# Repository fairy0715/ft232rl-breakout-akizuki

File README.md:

# ft232rl-breakout-akizuki

秋月電子製のFT232RLモジュール(通販コード:[101977](https://akizukidenshi.com/catalog/g/g101977/),[106693](https://akizukidenshi.com/catalog/g/g106693/))の互換基板です。

## 特徴
・接続端子をUSB mini-BからCに変更

・基本的に秋月電子で購入できる部品で作成可能

・表面実装部品を裏面に配置(本家と異なり、両面実装になっています)

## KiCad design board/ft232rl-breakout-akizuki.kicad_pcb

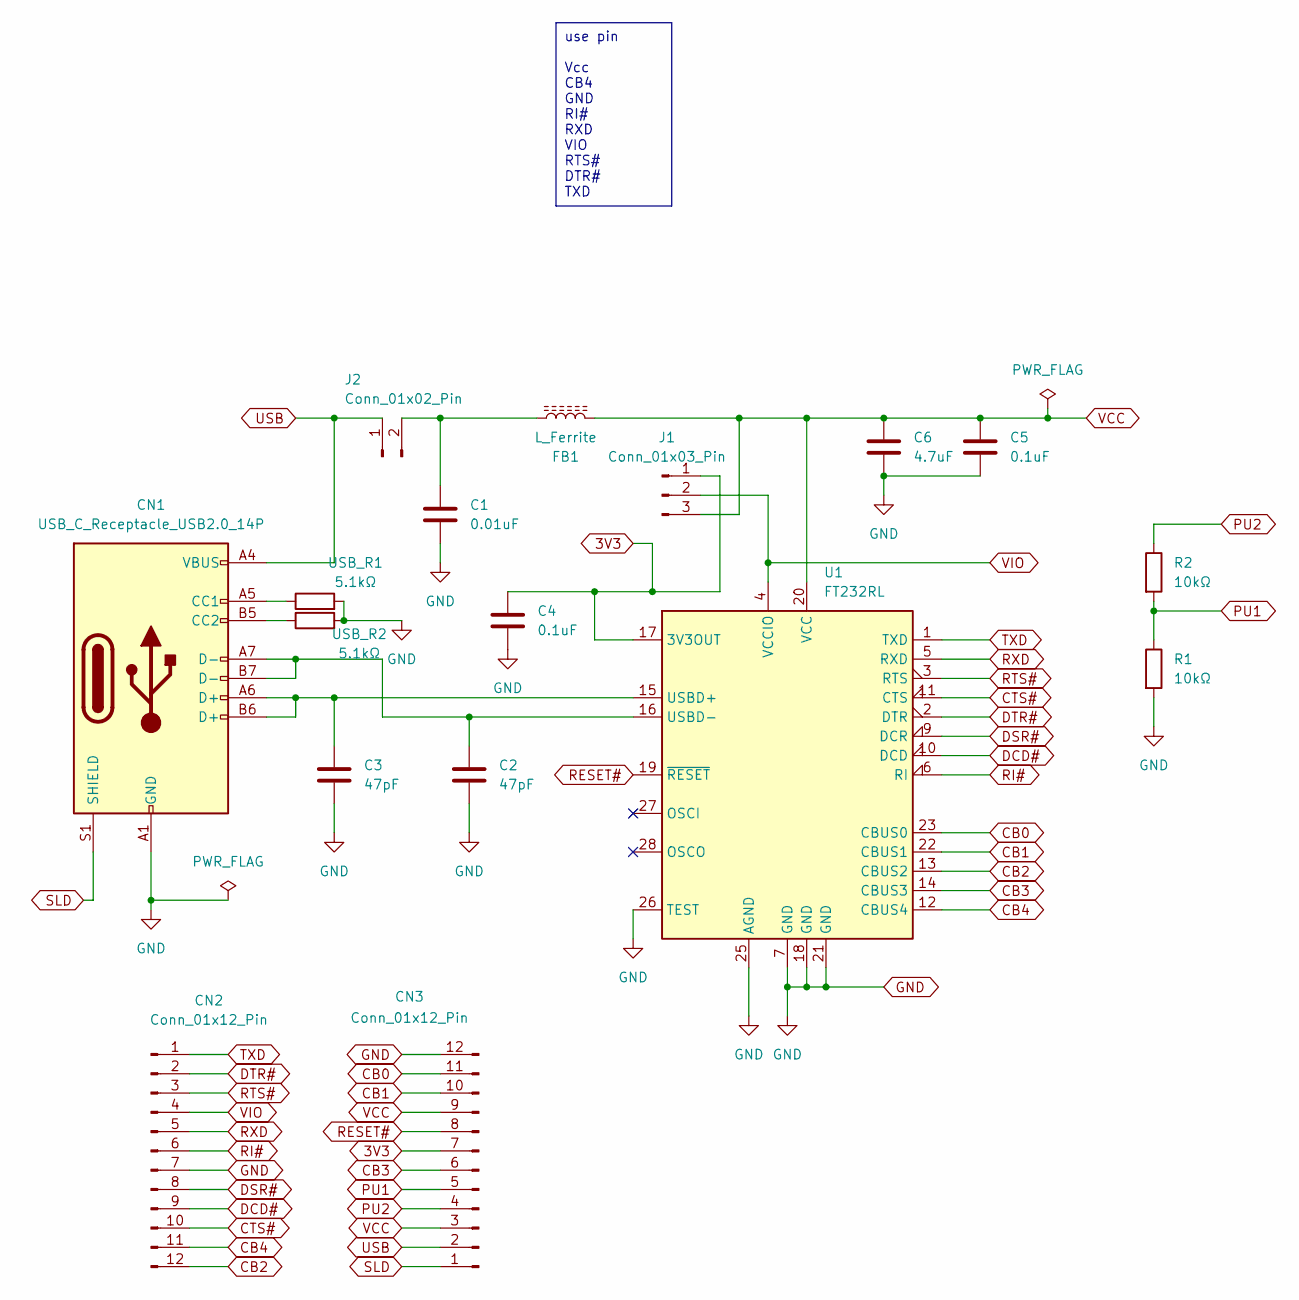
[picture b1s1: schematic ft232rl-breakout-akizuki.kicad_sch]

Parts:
C1: 0.01uF; C_0805_2012Metric_Pad1.18x1.45mm_HandSolder
C2, C3: 47pF; C_0805_2012Metric_Pad1.18x1.45mm_HandSolder
C4, C5: 0.1uF; C_0805_2012Metric_Pad1.18x1.45mm_HandSolder
C6: 4.7uF; C_0805_2012Metric_Pad1.18x1.45mm_HandSolder
CN1: USB_C_Receptacle_USB2.0_14P; USB_C_Receptacle_GCT_USB4105-xx-A_16P_TopMnt_Horizontal
CN2, CN3: Conn_01x12_Pin; PinHeader_1x12_P2.54mm_Vertical
FB1: L_Ferrite; C_0805_2012Metric_Pad1.18x1.45mm_HandSolder
J1: Conn_01x03_Pin; PinHeader_1x03_P2.54mm_Vertical
J2: Conn_01x02_Pin; PinHeader_1x02_P2.54mm_Vertical
R1, R2: 10kΩ; R_0805_2012Metric_Pad1.20x1.40mm_HandSolder
U1: FT232RL; SSOP-28_5.3x10.2mm_P0.65mm
USB_R1, USB_R2: 5.1kΩ; R_0805_2012Metric_Pad1.20x1.40mm_HandSolder

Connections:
3V3: C4.1, CN3.7, J1.1, U1.17 (3V3OUT)
CB0: CN3.11, U1.23 (CBUS0)
CB1: CN3.10, U1.22 (CBUS1)
CB2: CN2.12, U1.13 (CBUS2)
CB3: CN3.6, U1.14 (CBUS3)
CB4: CN2.11, U1.12 (CBUS4)
CTS#: CN2.10, U1.11 (CTS)
DCD#: CN2.9, U1.10 (DCD)
DSR#: CN2.8, U1.9 (DCR)
DTR#: CN2.2, U1.2 (DTR)
GND: C1.2, C2.2, C3.2, C4.2, C5.2, C6.2, CN1.A1 (GND), CN1.A12 (GND), CN1.B1 (GND), CN1.B12 (GND), CN2.7, CN3.12, R1.2, U1.7 (GND), U1.18 (GND), U1.21 (GND), U1.25 (AGND), U1.26 (TEST), USB_R1.2, USB_R2.2
unnamed: CN1.A5 (CC1), USB_R1.1
unnamed: CN1.B5 (CC2), USB_R2.1
unnamed: C1.1, FB1.2, J2.2
unnamed: C3.1, CN1.A6 (D+), CN1.B6 (D+), U1.15 (USBD+)
unnamed: C2.1, CN1.A7 (D-), CN1.B7 (D-), U1.16 (USBD-)
PU1: CN3.5, R1.1, R2.2
PU2: CN3.4, R2.1
RESET#: CN3.8, U1.19 (~RESET)
RI#: CN2.6, U1.6 (RI)
RTS#: CN2.3, U1.3 (RTS)
RXD: CN2.5, U1.5 (RXD)
SLD: CN1.S1 (SHIELD), CN3.1
TXD: CN2.1, U1.1 (TXD)
USB: CN1.A4 (VBUS), CN1.A9 (VBUS), CN1.B4 (VBUS), CN1.B9 (VBUS), CN3.2, J2.1
VCC: C5.1, C6.1, CN3.3, CN3.9, FB1.1, J1.3, U1.20 (VCC)
VIO: CN2.4, J1.2, U1.4 (VCCIO)

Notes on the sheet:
use pin Vcc CB4 GND RI# RXD VIO RTS# DTR# TXD

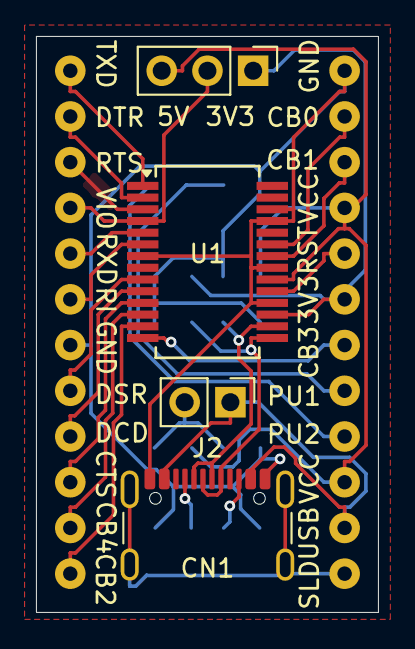
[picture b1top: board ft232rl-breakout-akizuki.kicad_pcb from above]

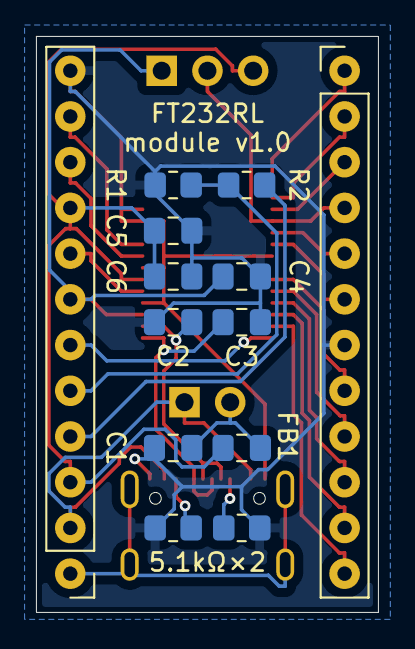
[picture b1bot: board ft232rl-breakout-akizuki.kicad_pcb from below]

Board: 2 copper layers, 19.0 x 32.0 mm, 17 parts (13 on the bottom side), 27 nets.

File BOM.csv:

部品番号,値,サイズ,数量
C1,0.01uF,2012サイズ,1
"C2,C3",47pF,2012サイズ,2
"C4,C5",0.1uF,2012サイズ,2
C6,4.7uF,2012サイズ,1
CN1,5077CR-16-SMC2-BK-TR,-,1
"CN2,CN3",1x12 ピンヘッダ,2.54mmピッチ,2
FB1,BLM21PG331SN,2012サイズ,1
J1,1x3 ピンヘッダ,2.54mmピッチ,1
J2,1x2 ピンヘッダ,2.54mmピッチ,1
"R1,R2",10kΩ,2012サイズ,2
U1,FT232RL or FT232RNL,SOP-28,1
"USB_R1,USB_R2",5.1kΩ,2012サイズ,2
